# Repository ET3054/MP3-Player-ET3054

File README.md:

# MP3-Player-ET3054

Einrichtung:          		Hochschule für Wirtschaft und Recht Berlin

Jahrgang:                  	2024

Studierende:               	Bruno Storp
                           	Niclas Konzack
                           
Modul:                     	ET3054 Produktentwicklung

Zielsetzung des Projekts:  	Entwicklung eines MP3-Players, welcher auch leistungsstärkere Kopfhöher (Benchmark Sennheiser HD650) ohne qualitative Einschränkungen betreiben kann

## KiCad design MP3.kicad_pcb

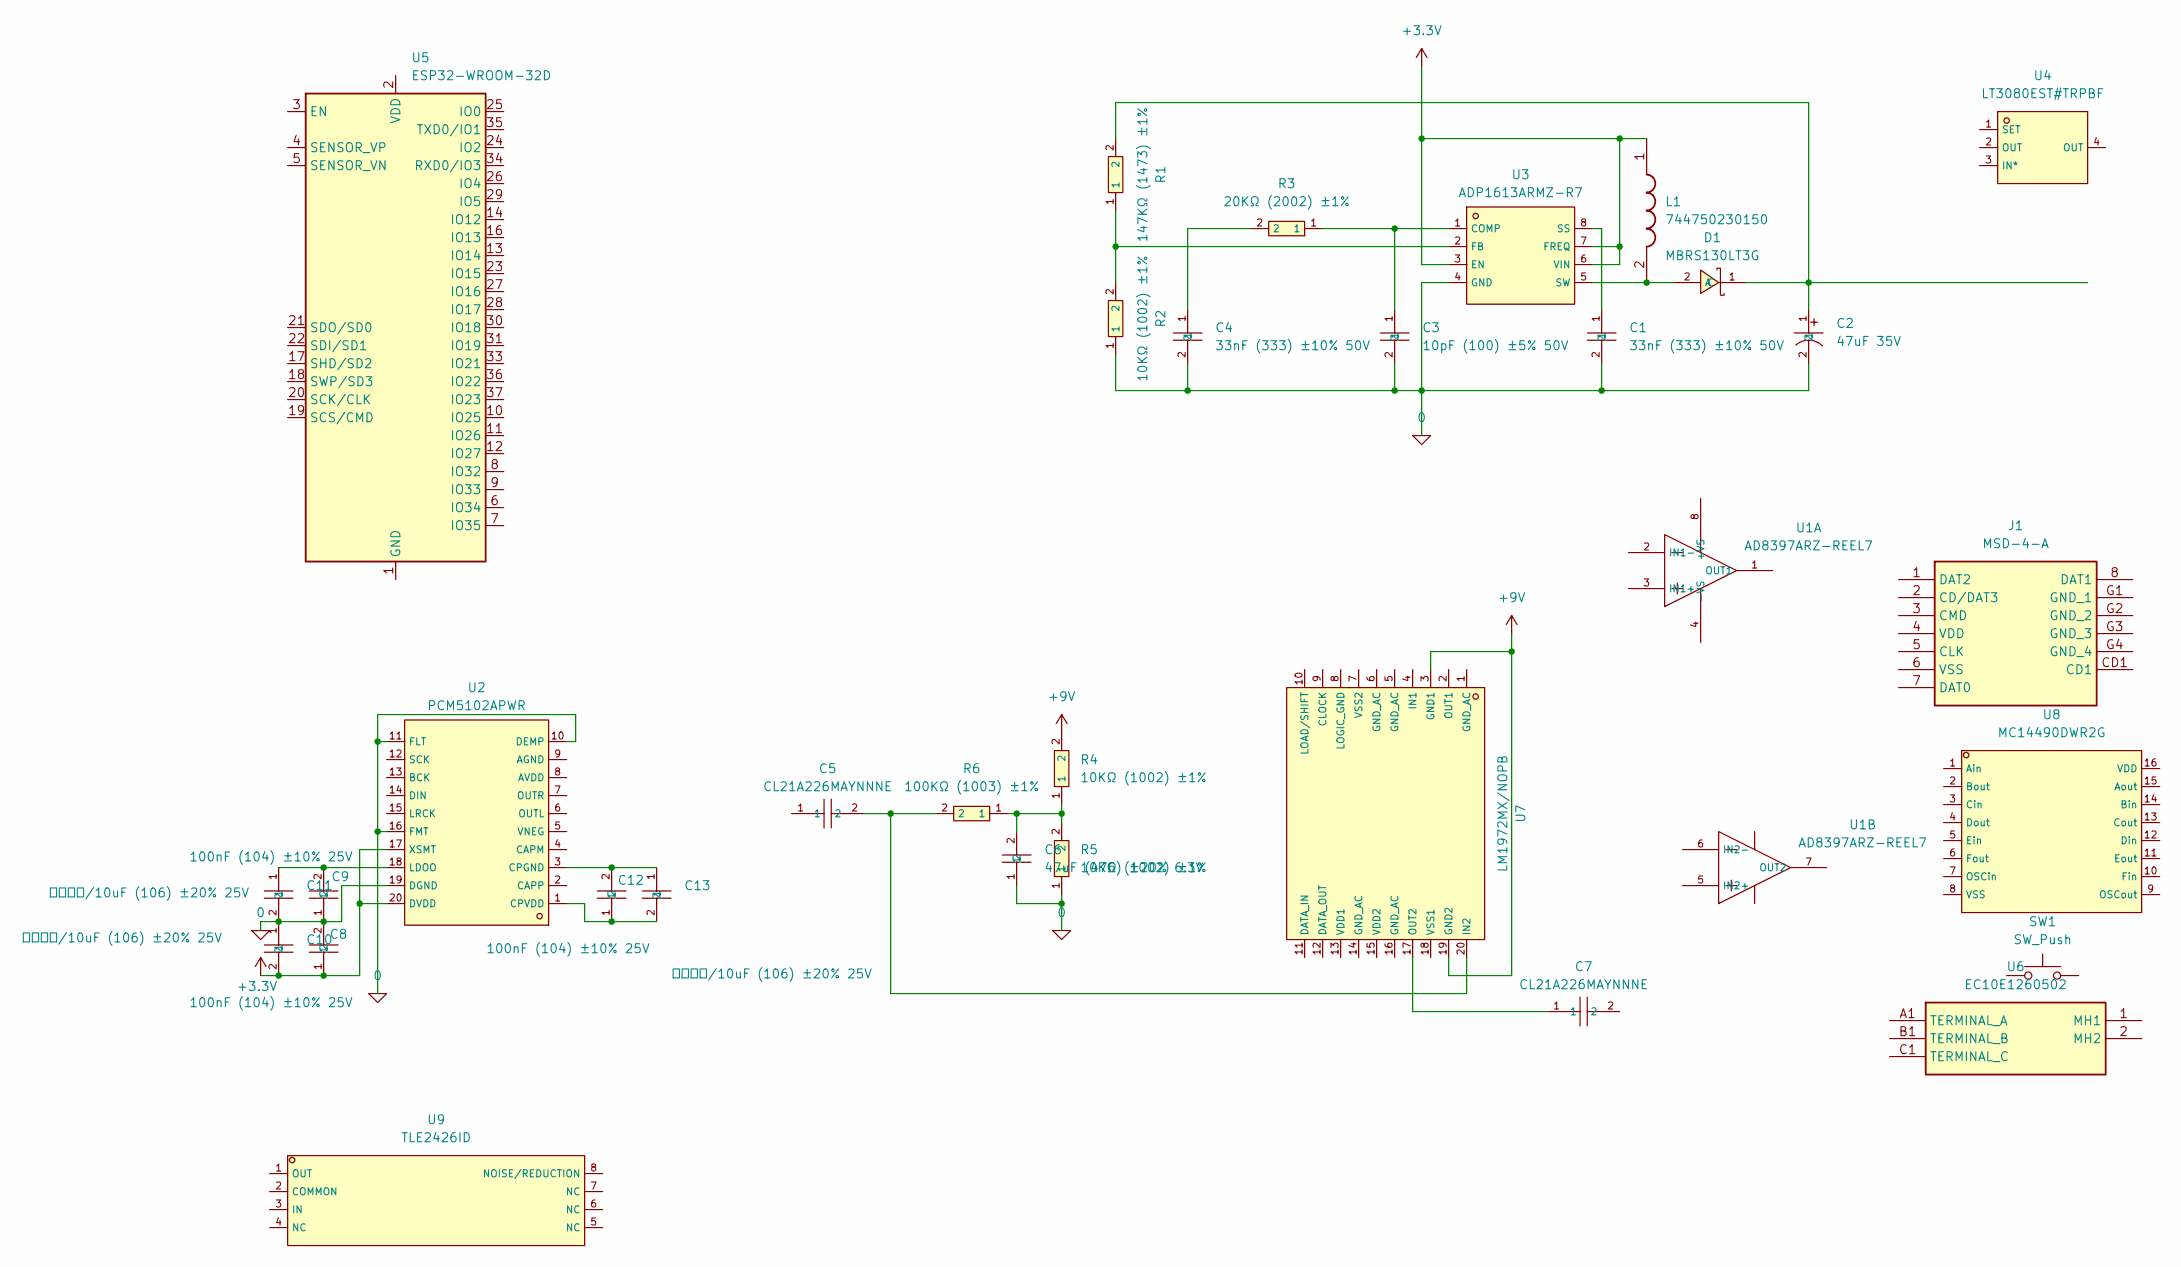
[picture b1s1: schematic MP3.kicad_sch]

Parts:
C1, C4: 33nF (333) ±10% 50V; C1614_C0603; LCSC C1614
C2: 47uF 35V; C40063_CAP-TH_BD5_0-P2_00-D0_8-FD; LCSC C40063
C3: 10pF (100) ±5% 50V; C1634_C0603; LCSC C1634
C5, C7: CL21A226MAYNNNE; C602037_C0805; LCSC C602037
C6: 47uF (476) ±20% 6.3V; C16780_C0805; LCSC C16780
C8, C9, C12: 100nF (104) ±10% 25V; C1590_C0603; LCSC C1590
C10, C11, C13: 贴片电容/10uF (106) ±20% 25V; C76614_C0603; LCSC C76614
D1: MBRS130LT3G; C51771_SMB_L4_6-W3_6-LS5_3-RD; LCSC C51771
J1: MSD-4-A; MSD4A; Mouser Part Number 179-MSD-4-A
L1: 744750230150; Mouser Part Number 710-744750230150
R1: 147KΩ (1473) ±1%; C22878_R0603; LCSC C22878
R2, R4, R5: 10KΩ (1002) ±1%; C17414_R0805; LCSC C17414
R3: 20KΩ (2002) ±1%; C4184_R0603; LCSC C4184
R6: 100KΩ (1003) ±1%; C25803_R0603; LCSC C25803
SW1: SW_Push; SW_Cherry_MX_PCB_1.00u
U1: AD8397ARZ-REEL7; C521305_SOIC-8_L4_9-W3_9-P1_27-LS6_0-BL; LCSC C521305
U2: PCM5102APWR; C107671_TSSOP-20_L6_5-W4_4-P0_65-LS6_4-BL; LCSC C107671
U3: ADP1613ARMZ-R7; C132279_MSOP-8_L3_0-W3_0-P0_65-LS4_9-BL; LCSC C132279
U4: LT3080EST#TRPBF; C107704_SOT-223_L6_5-W3_5-P2_30-LS7_0-BR_ST_VNL5050N3TR-E; LCSC C107704
U5: ESP32-WROOM-32D
U6: EC10E1260502; Mouser Part Number 688-EC10E1260502
U7: LM1972MX/NOPB; C2649339_SOIC-20_L13_0-W7_6-P1_27-LS10_3-BL; LCSC C2649339
U8: MC14490DWR2G; C223556_SOIC-16_L10_3-W7_5-P1_27-LS10_3-BL; LCSC C223556
U9: TLE2426ID; C353015_SOIC-8_L4_9-W3_9-P1_27-LS6_0-BL; LCSC C353015

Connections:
0: C1.2, C2.2, C3.2, C4.2, C6.1, C8.2, C9.1, C10.1, C11.2, R2.1, R5.1, U2.10 (DEMP), U2.11 (FLT), U2.16 (FMT), U2.19 (DGND), U3.4 (GND)
+3.3V: C8.1, C10.2, L1.1, U2.17 (XSMT), U2.20 (DVDD), U3.3 (EN), U3.6 (VIN), U3.7 (FREQ)
+9V: R4.2, U7.3 (GND1), U7.19 (GND2)
unnamed: C4.1, R3.2
unnamed: C6.2, R4.1, R5.2, R6.1
unnamed: D1.2 (A), L1.2, U3.5 (SW)
unnamed: C2.1, D1.1 (C), R1.2
unnamed: C12.2, C13.1, U2.3 (CPGND)
unnamed: C12.1, C13.2, U2.1 (CPVDD)
unnamed: C9.2, C11.1, U2.18 (LDOO)
unnamed: C3.1, R3.1, U3.1 (COMP)
unnamed: R1.1, R2.2, U3.2 (FB)
unnamed: C1.1, U3.8 (SS)
unnamed: U5.1 (GND), U5.15 (GND), U5.38 (GND), U5.39 (GND)
unnamed: C5.2 (2_2), R6.2, U7.20 (IN2)
unnamed: C7.1 (1_1), U7.17 (OUT2)

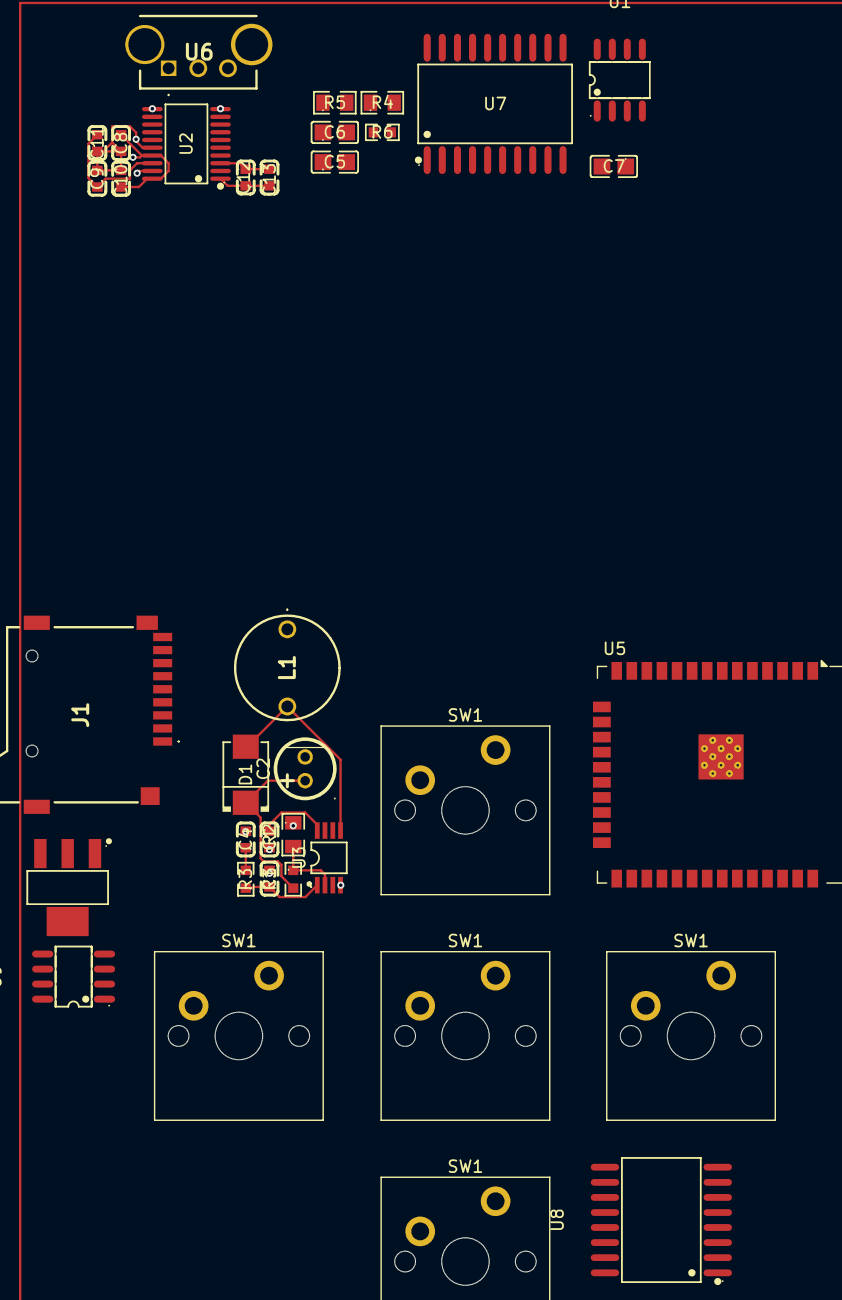
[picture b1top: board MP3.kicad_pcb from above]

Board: 4 copper layers, 36 parts (0 on the bottom side), 16 nets.

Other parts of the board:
SW1#2, SW1#3, SW1#4, SW1#5: SW_Push; SW_Cherry_MX_PCB_1.00u
